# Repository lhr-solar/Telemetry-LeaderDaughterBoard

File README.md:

# Telemetry-LeaderDaughterboard
Author: Andrew Nguyen

## BOM
[**Interactive BOM (Must download and open in browser)**](bom/ibom.html)

[**Mouser Cart**]

## Connectors
| # | Name | Type | Ideal Voltage | Notes |
| - | - | - | - | - |

## PCB

## Schematic

## Additional Notes

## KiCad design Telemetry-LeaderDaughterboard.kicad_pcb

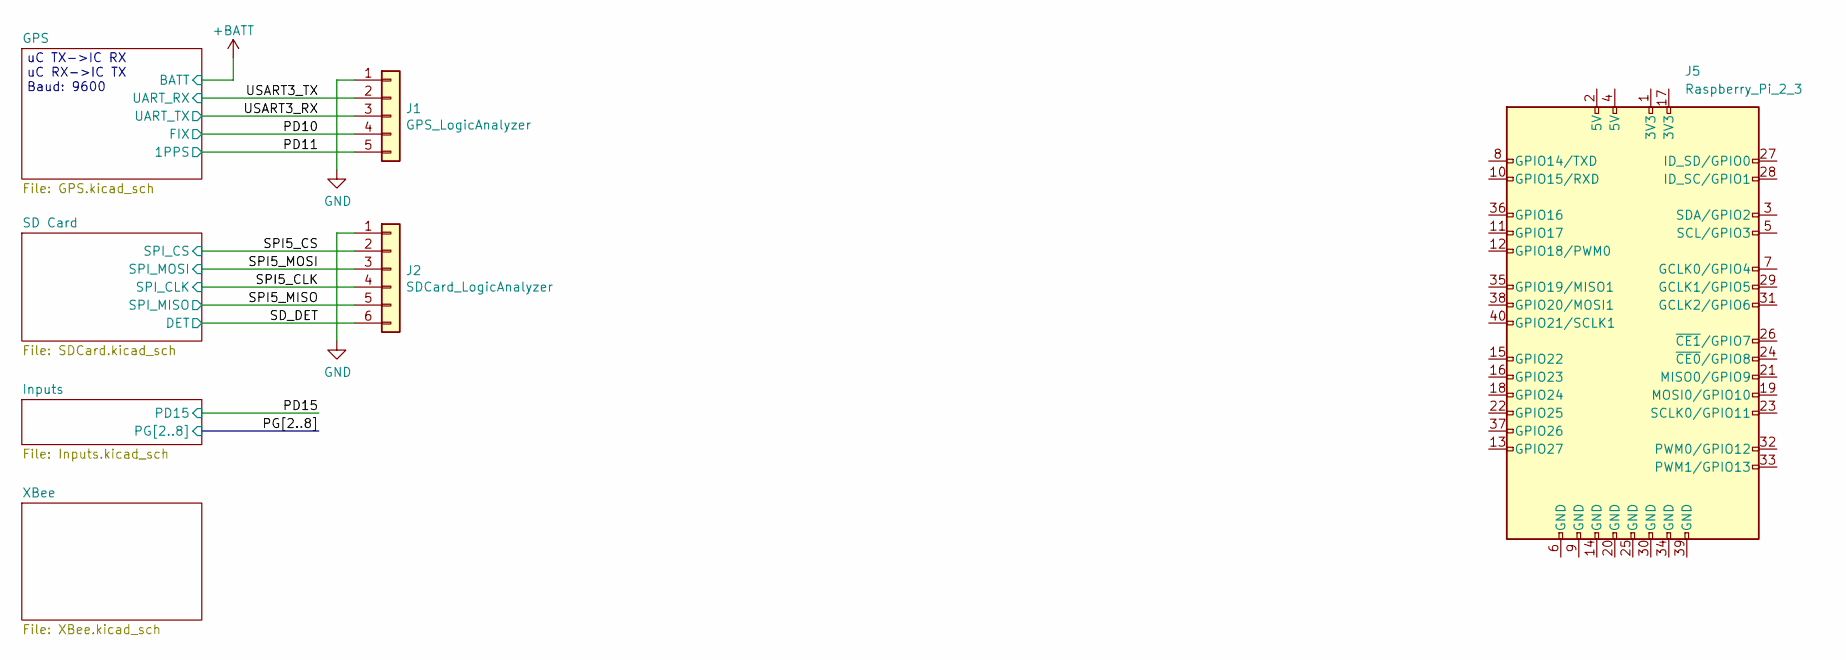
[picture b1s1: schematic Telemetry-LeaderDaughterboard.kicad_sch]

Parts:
J1: GPS_LogicAnalyzer; PinHeader_1x05_P2.54mm_Vertical
J2: SDCard_LogicAnalyzer; PinHeader_1x06_P2.54mm_Vertical
J5: Raspberry_Pi_2_3

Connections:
/PD10: J1.4; also elsewhere on the board
/PD11: J1.5; also elsewhere on the board
/SD_DET: J2.6; also elsewhere on the board
/SPI5_CLK: J2.4; also elsewhere on the board
/SPI5_CS: J2.2; also elsewhere on the board
/SPI5_MISO: J2.5; also elsewhere on the board
/SPI5_MOSI: J2.3; also elsewhere on the board
/USART3_RX: J1.3; also elsewhere on the board
/USART3_TX: J1.2; also elsewhere on the board
GND: J1.1, J2.1; also elsewhere on the board

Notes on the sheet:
uC TX->IC RX uC RX->IC TX Baud: 9600

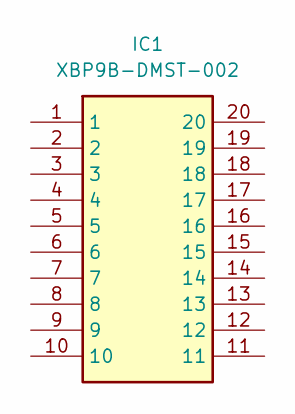
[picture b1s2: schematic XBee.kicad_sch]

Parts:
IC1: XBP9B-DMST-002; Mouser Part Number 888-XBP9B-DMST-002

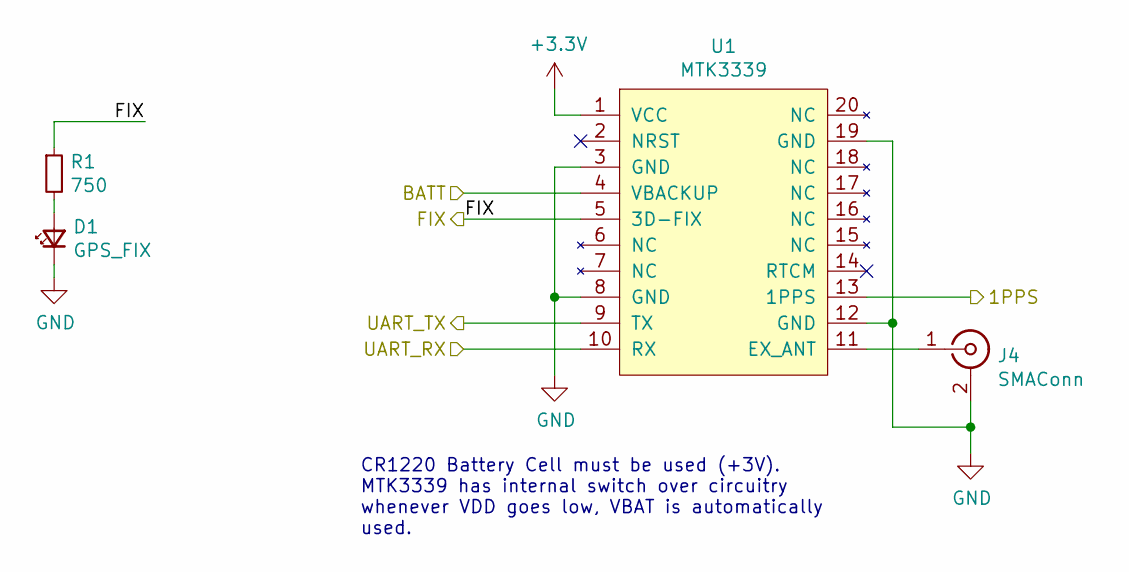
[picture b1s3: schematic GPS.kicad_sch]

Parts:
D1: GPS_FIX; LED_0805_2012Metric
J4: SMAConn; SMA_Amphenol_132203-12_Horizontal
R1: 750; R_0805_2012Metric
U1: MTK3339; FGPMMOPA6H

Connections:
+3.3V: U1.1 (VCC); also elsewhere on the board
+BATT: U1.4 (VBACKUP)
/PD10: R1.1, U1.5 (3D-FIX); also elsewhere on the board
/PD11: U1.13 (1PPS); also elsewhere on the board
/USART3_RX: U1.9 (TX); also elsewhere on the board
/USART3_TX: U1.10 (RX); also elsewhere on the board
GND: D1.1 (K), J4.2 (Ext), U1.3 (GND), U1.8 (GND), U1.12 (GND), U1.19 (GND); also elsewhere on the board
unnamed: D1.2 (A), R1.2
unnamed: J4.1 (In), U1.11 (EX_ANT)

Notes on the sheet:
CR1220 Battery Cell must be used (+3V). MTK3339 has internal switch over circuitry whenever VDD goes low, VBAT is automatically used.

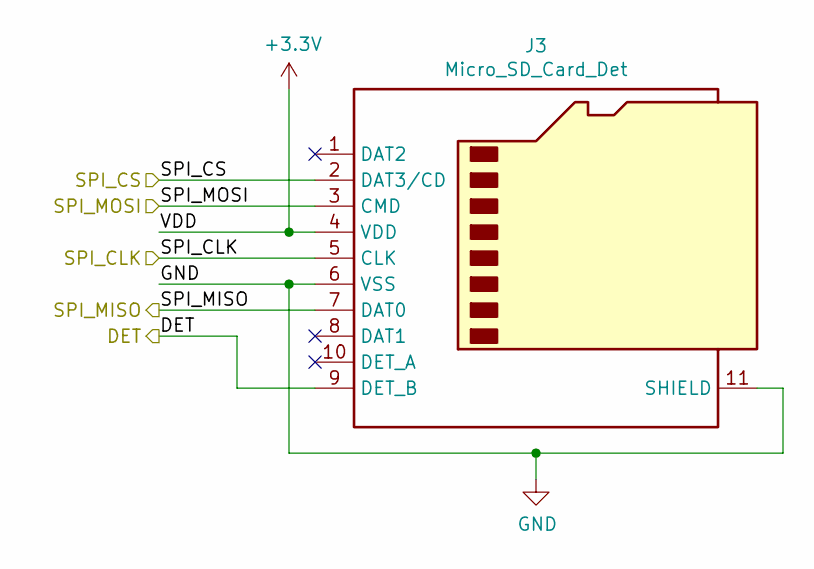
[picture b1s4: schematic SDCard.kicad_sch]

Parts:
J3: Micro_SD_Card_Det; microSD_HC_Hirose_DM3AT-SF-PEJM5

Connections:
+3.3V: J3.4 (VDD); also elsewhere on the board
/SD_DET: J3.9 (DET_B); also elsewhere on the board
/SPI5_CLK: J3.5 (CLK); also elsewhere on the board
/SPI5_CS: J3.2 (DAT3/CD); also elsewhere on the board
/SPI5_MISO: J3.7 (DAT0); also elsewhere on the board
/SPI5_MOSI: J3.3 (CMD); also elsewhere on the board
GND: J3.6 (VSS), J3.11 (SHIELD); also elsewhere on the board

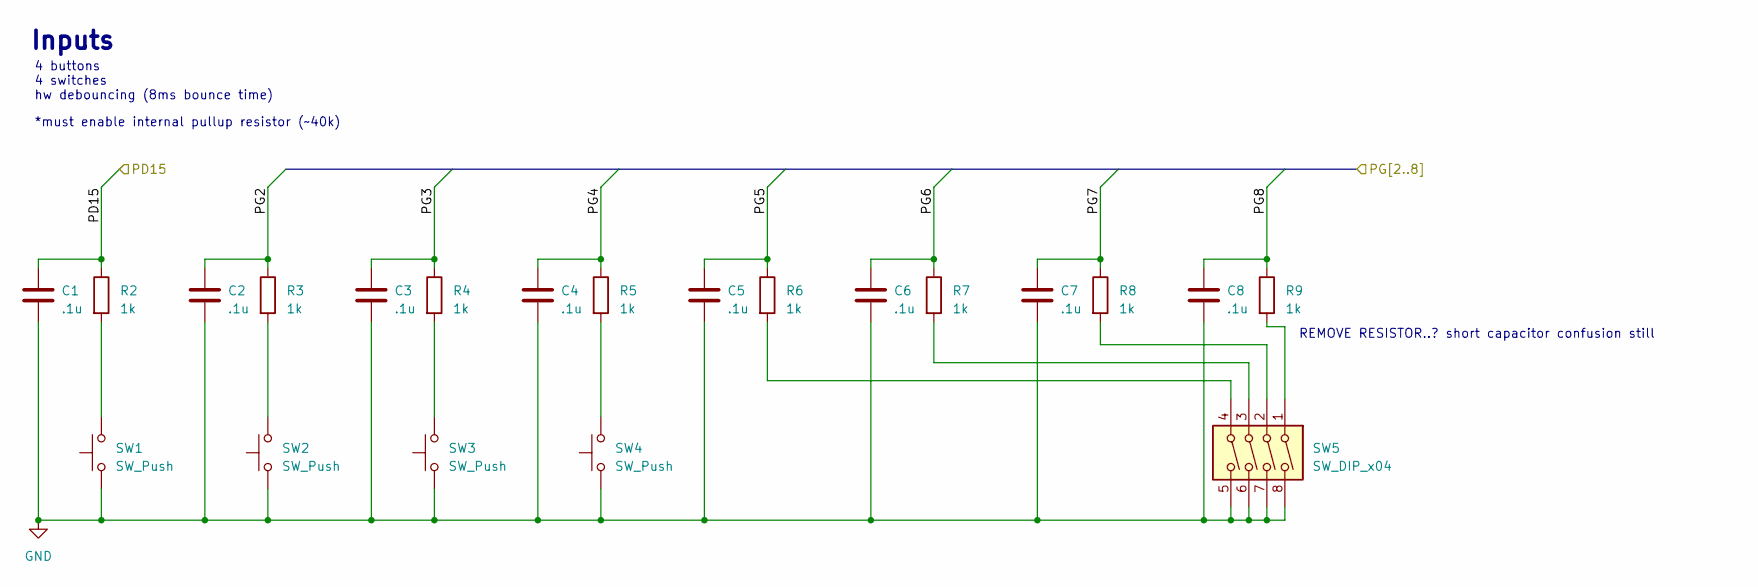
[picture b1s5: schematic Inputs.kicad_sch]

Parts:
C1, C2, C3, C4, C5, C6, C7, C8: .1u; C_0805_2012Metric
R2, R3, R4, R5, R6, R7, R8, R9: 1k; R_0805_2012Metric
SW1, SW2, SW3, SW4: SW_Push; SW_SPST_B3SL-1002P
SW5: SW_DIP_x04; SW_DIP_SPSTx04_Slide_6.7x11.72mm_W8.61mm_P2.54mm_LowProfile

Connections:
/PD15: C1.1, R2.1
/PG2: C2.1, R3.1
/PG3: C3.1, R4.1
/PG4: C4.1, R5.1
/PG5: C5.1, R6.1
/PG6: C6.1, R7.1
/PG7: C7.1, R8.1
/PG8: C8.1, R9.1
GND: C1.2, C2.2, C3.2, C4.2, C5.2, C6.2, C7.2, C8.2, SW1.1, SW2.1, SW3.1, SW4.1, SW5.5, SW5.6, SW5.7, SW5.8; also elsewhere on the board
unnamed: R2.2, SW1.2
unnamed: R3.2, SW2.2
unnamed: R4.2, SW3.2
unnamed: R5.2, SW4.2
unnamed: R6.2, SW5.4
unnamed: R7.2, SW5.3
unnamed: R8.2, SW5.2
unnamed: R9.2, SW5.1

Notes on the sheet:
*must enable internal pullup resistor (~40k)
Inputs
REMOVE RESISTOR..? short capacitor confusion still
4 buttons 4 switches hw debouncing (8ms bounce time)

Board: 2 copper layers, 29 parts (0 on the bottom side), 29 nets, no tracks yet.

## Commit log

2023-09-30 migration from old leader
2023-09-30 utsvt library linked
2023-09-30 xbee initial addition
